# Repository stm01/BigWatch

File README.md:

# BigWatch
ATMega328 based DCF 77 synched Clock with 3D-printed Segments
/***
Readme will follow!

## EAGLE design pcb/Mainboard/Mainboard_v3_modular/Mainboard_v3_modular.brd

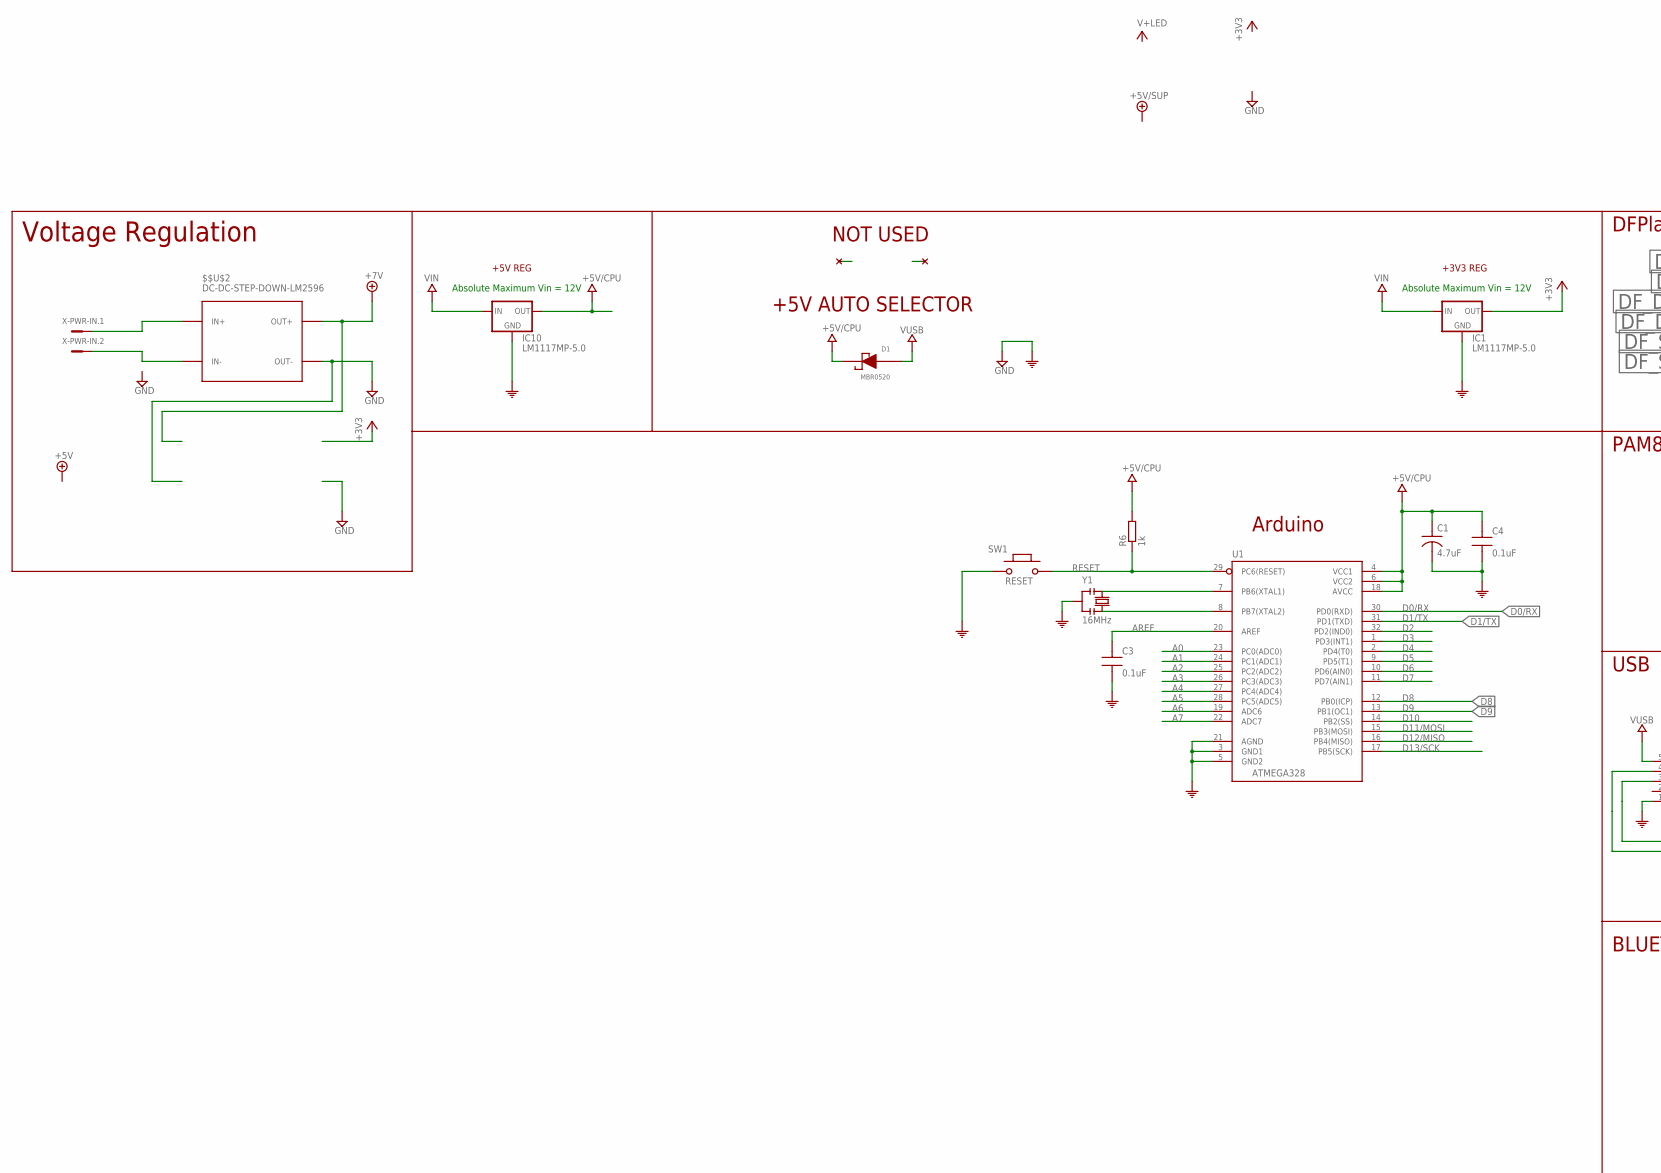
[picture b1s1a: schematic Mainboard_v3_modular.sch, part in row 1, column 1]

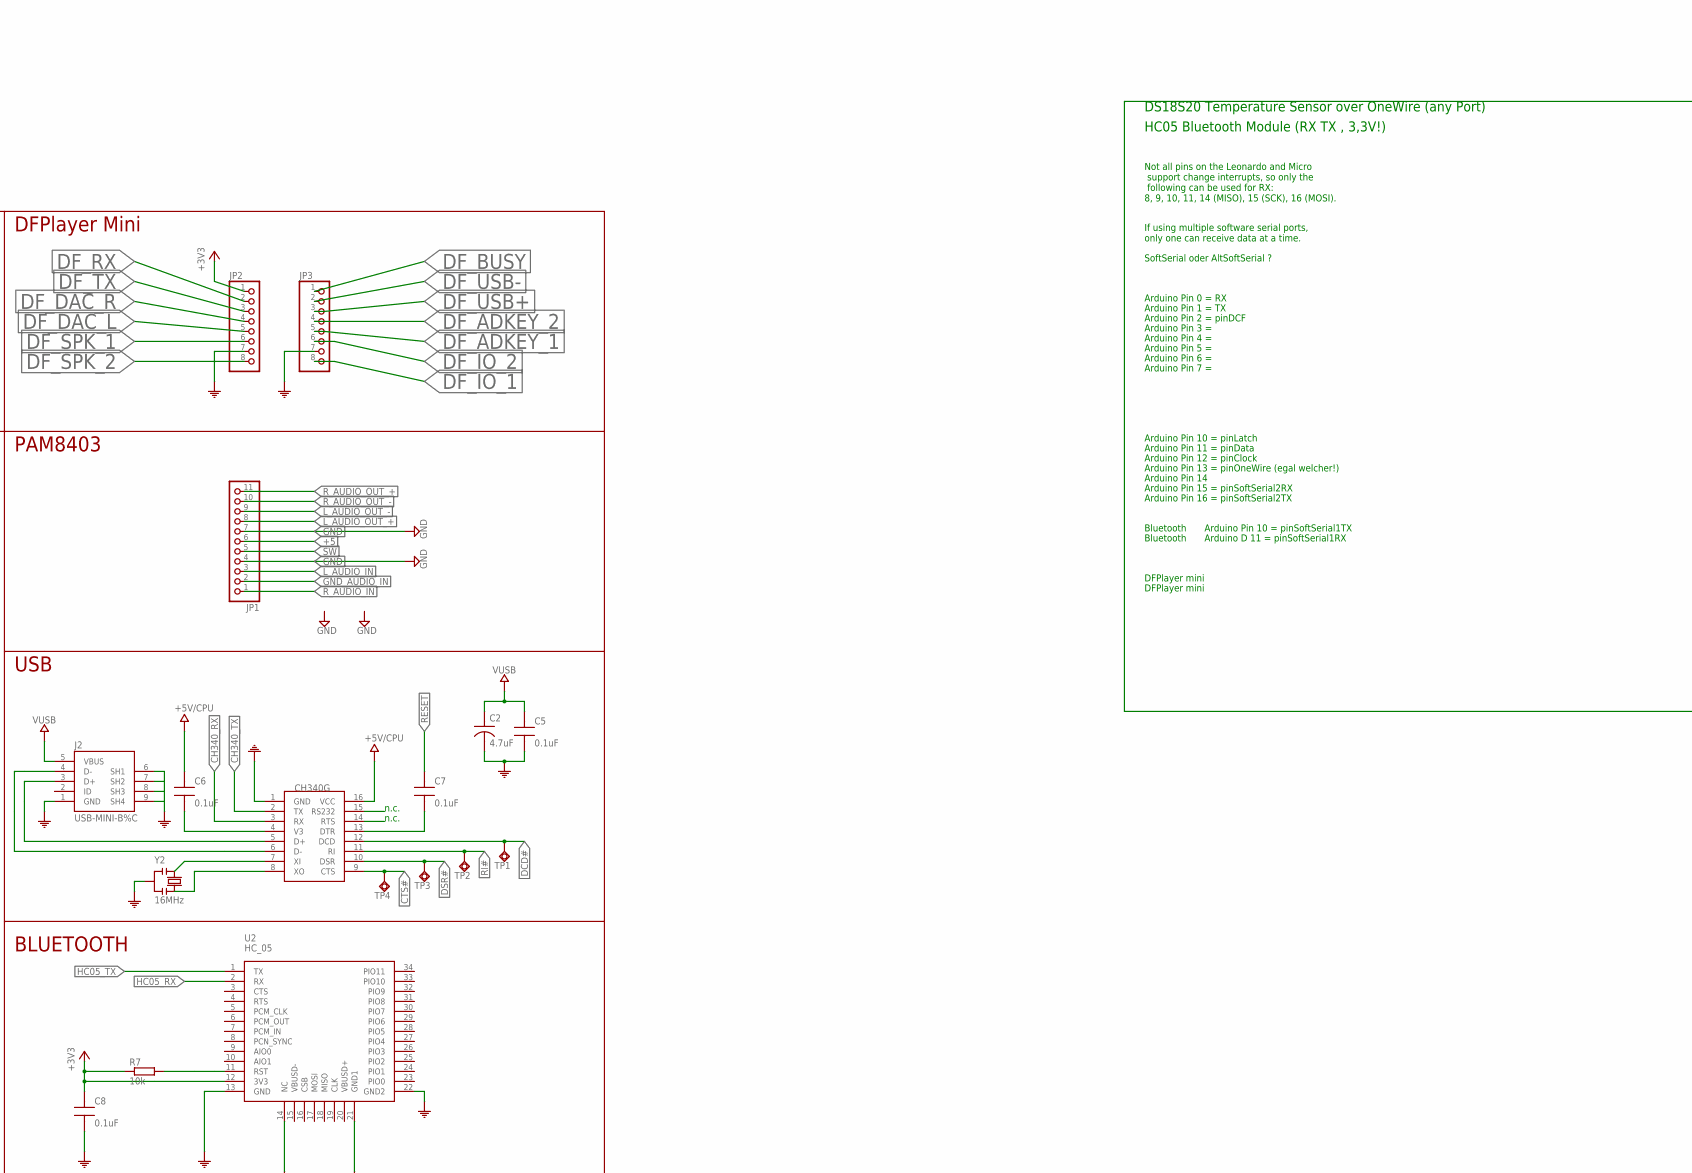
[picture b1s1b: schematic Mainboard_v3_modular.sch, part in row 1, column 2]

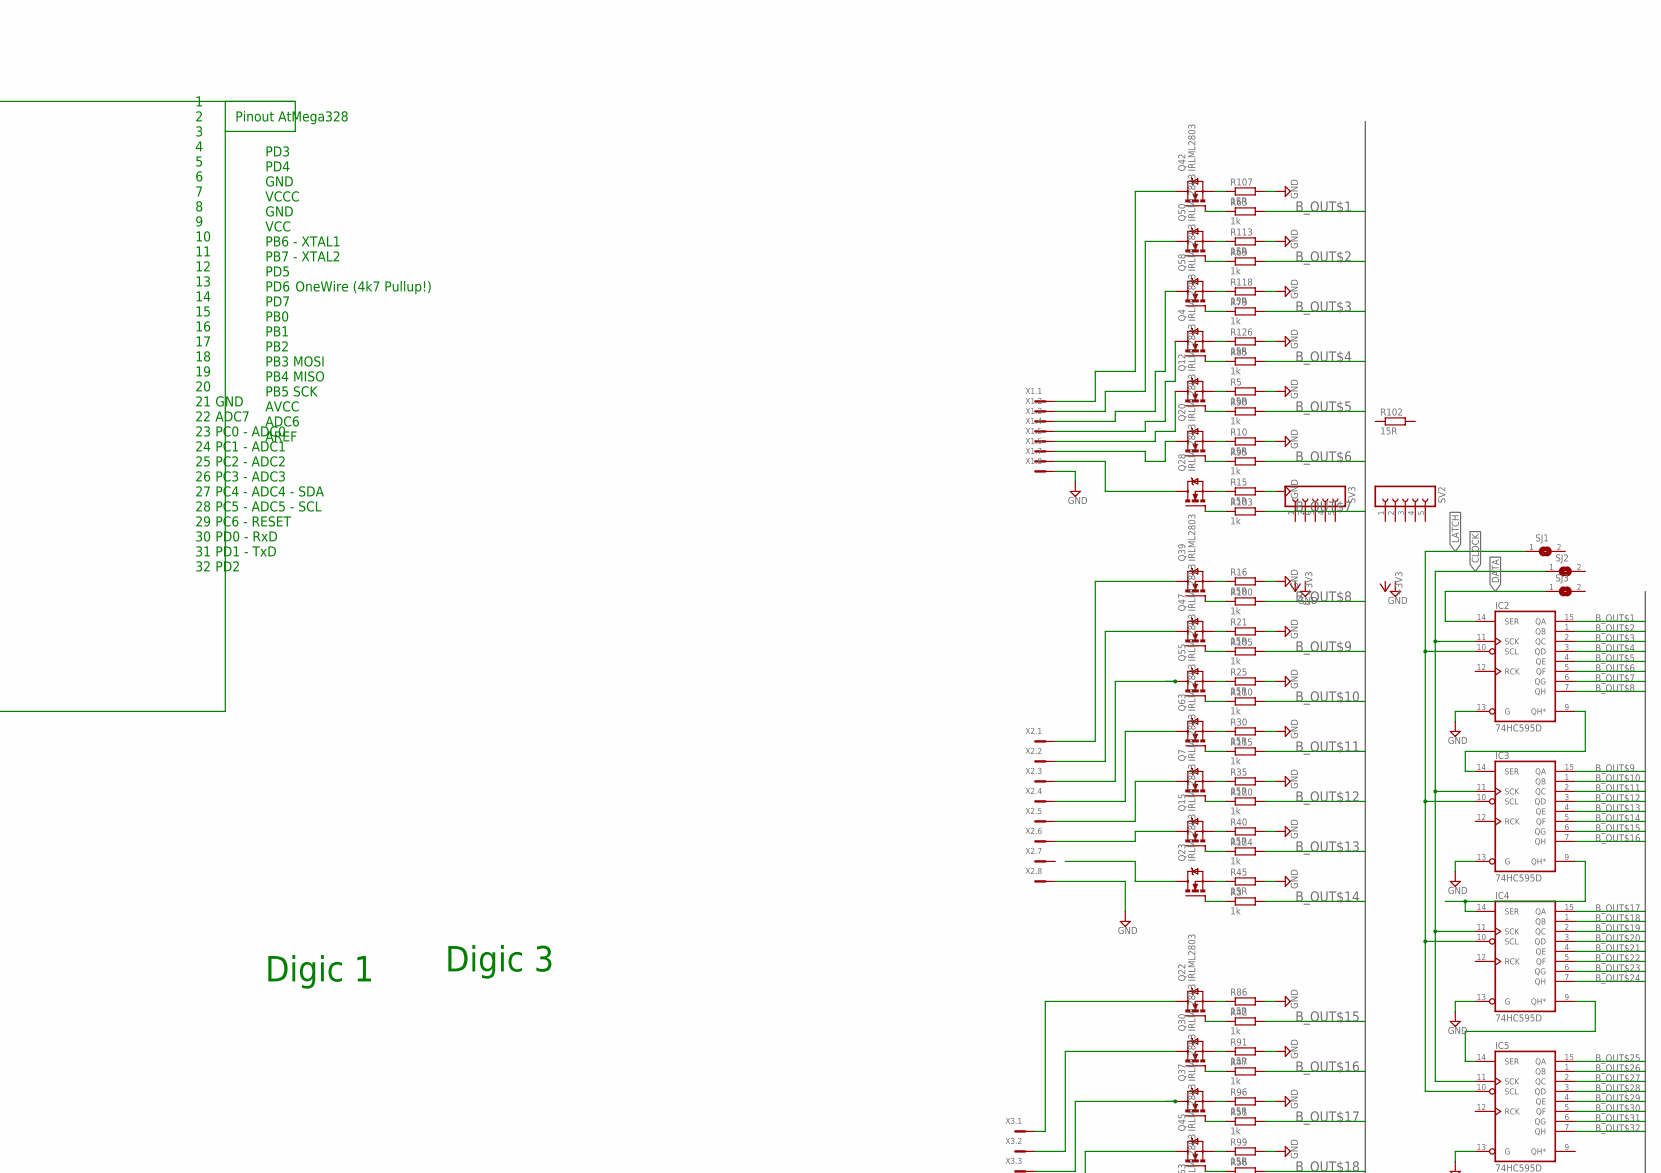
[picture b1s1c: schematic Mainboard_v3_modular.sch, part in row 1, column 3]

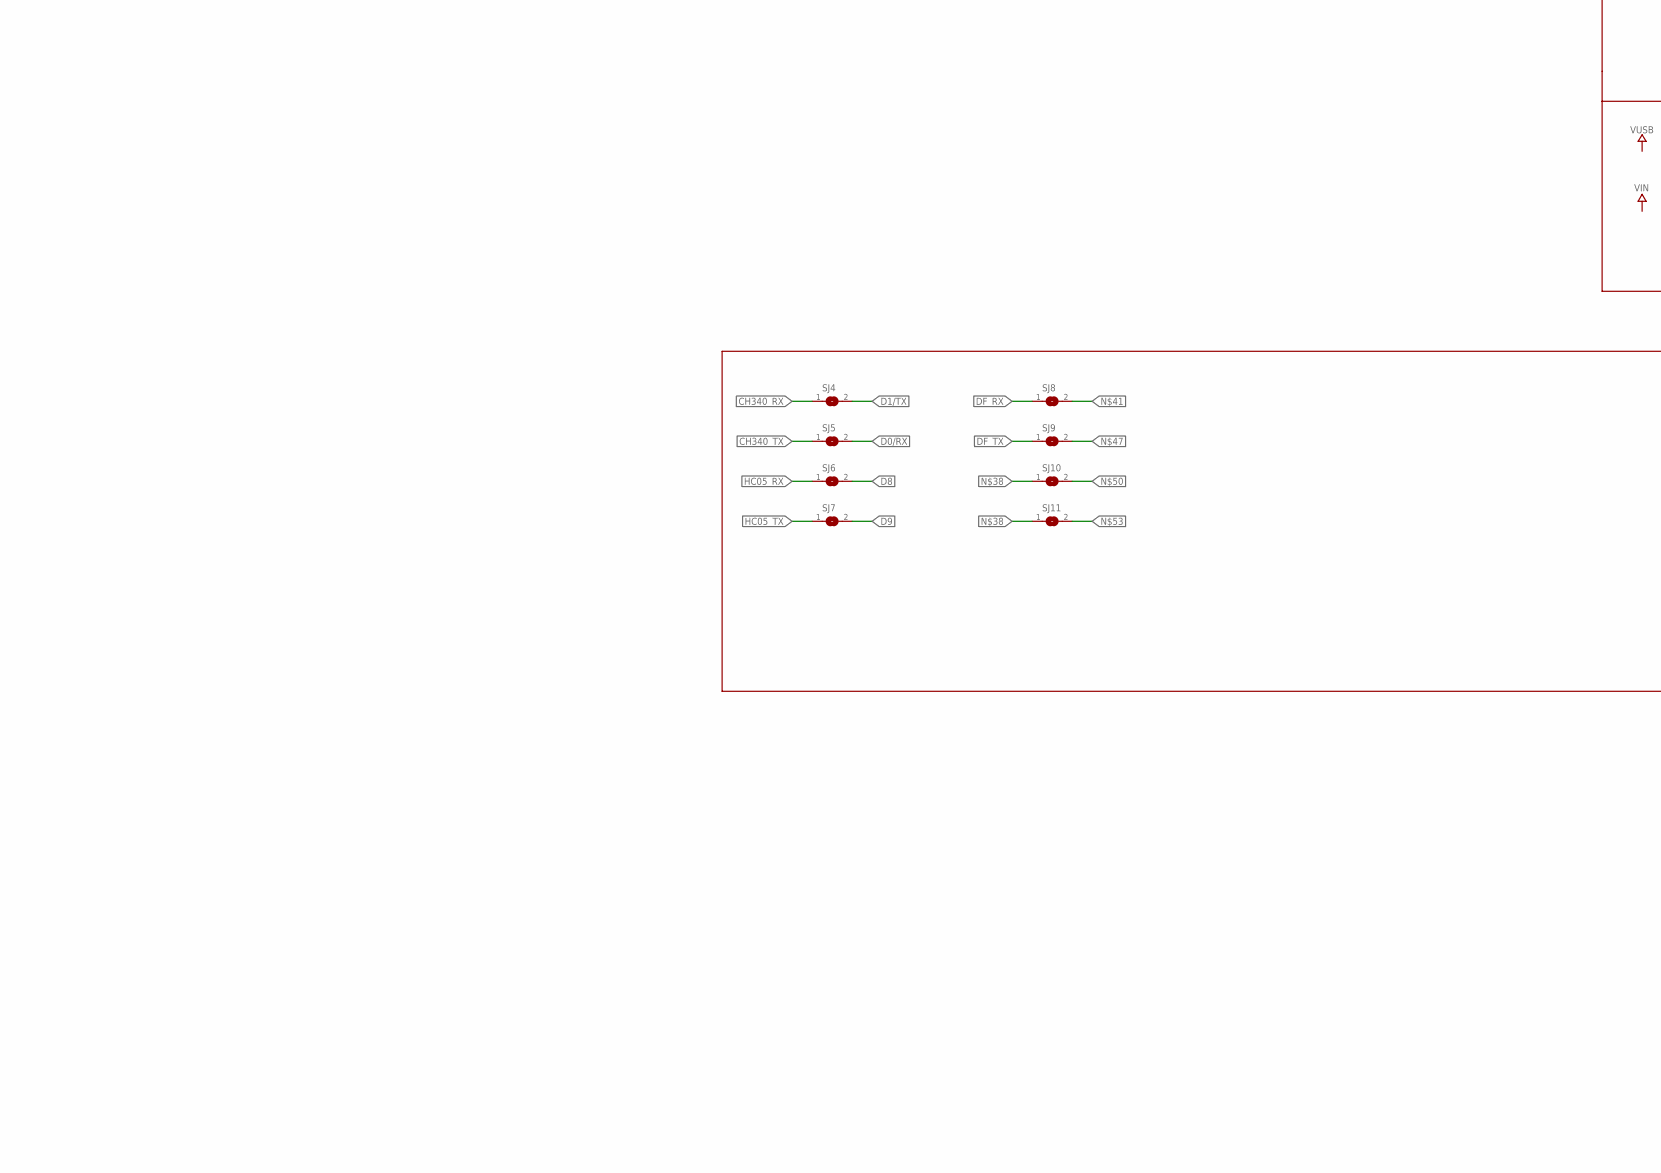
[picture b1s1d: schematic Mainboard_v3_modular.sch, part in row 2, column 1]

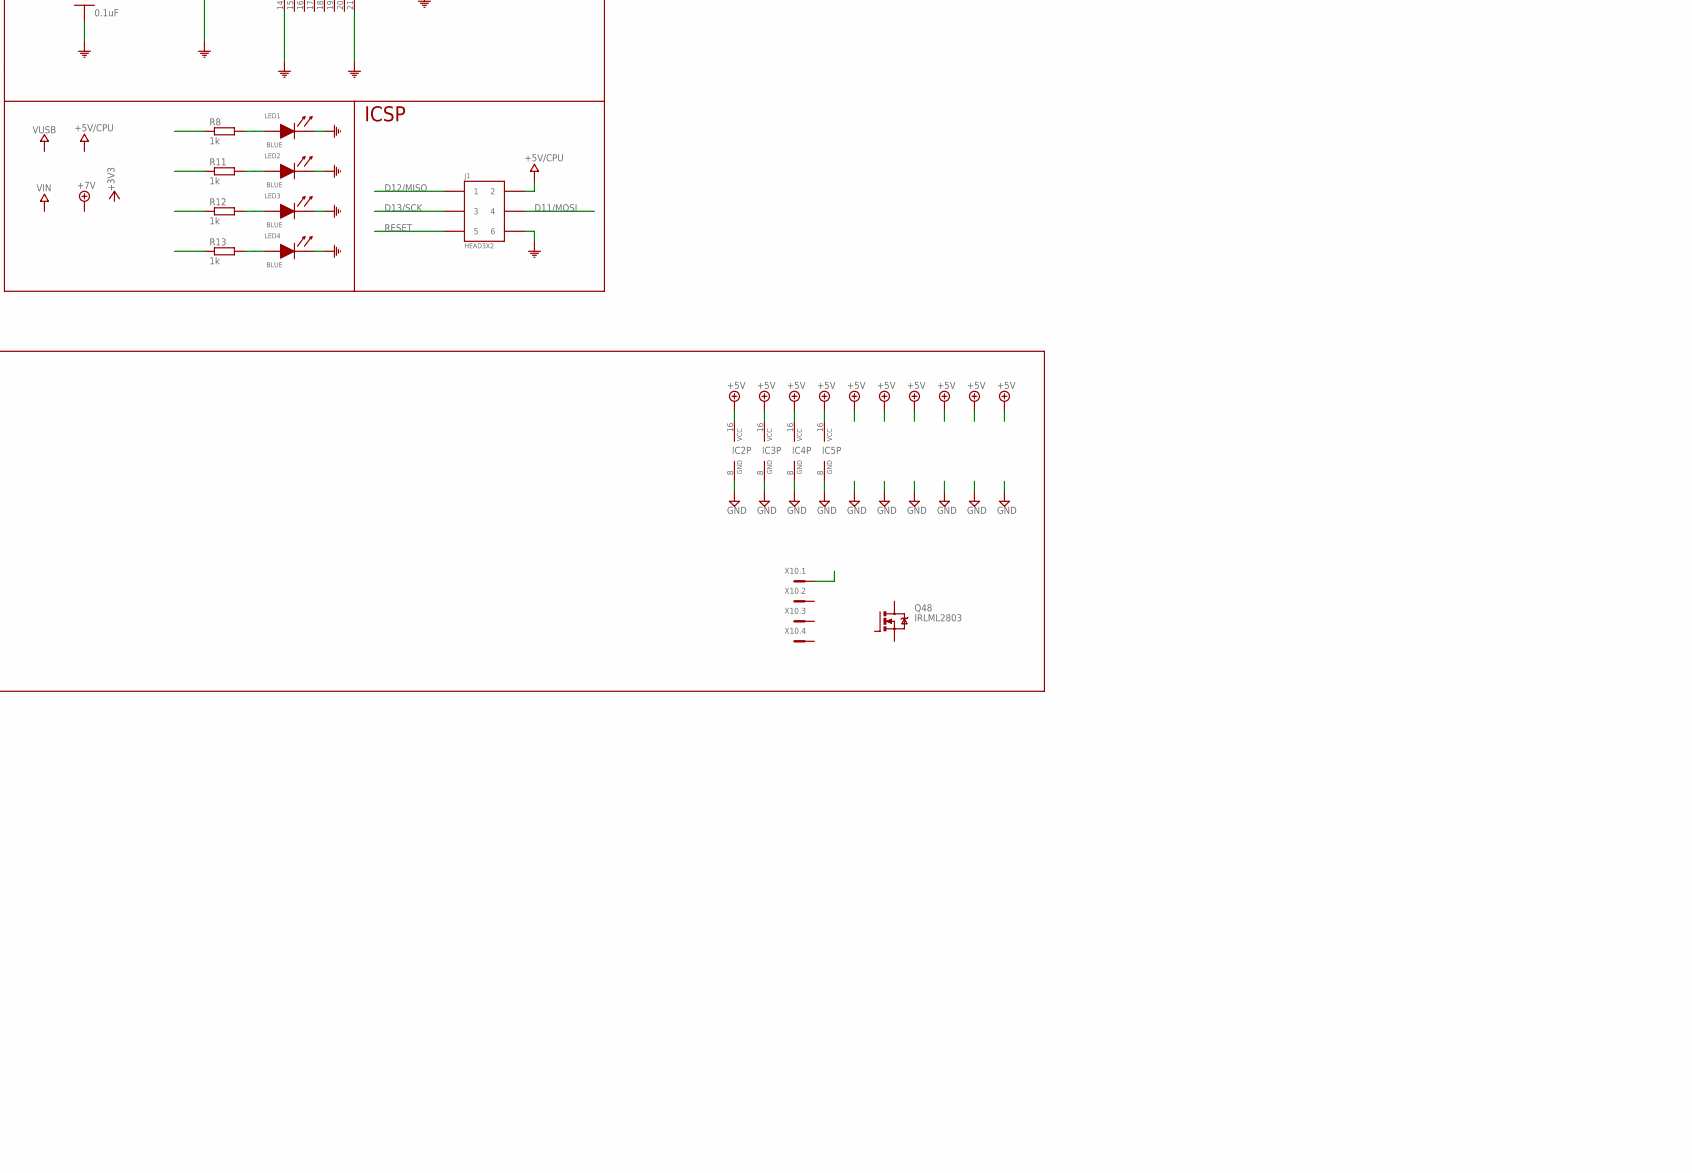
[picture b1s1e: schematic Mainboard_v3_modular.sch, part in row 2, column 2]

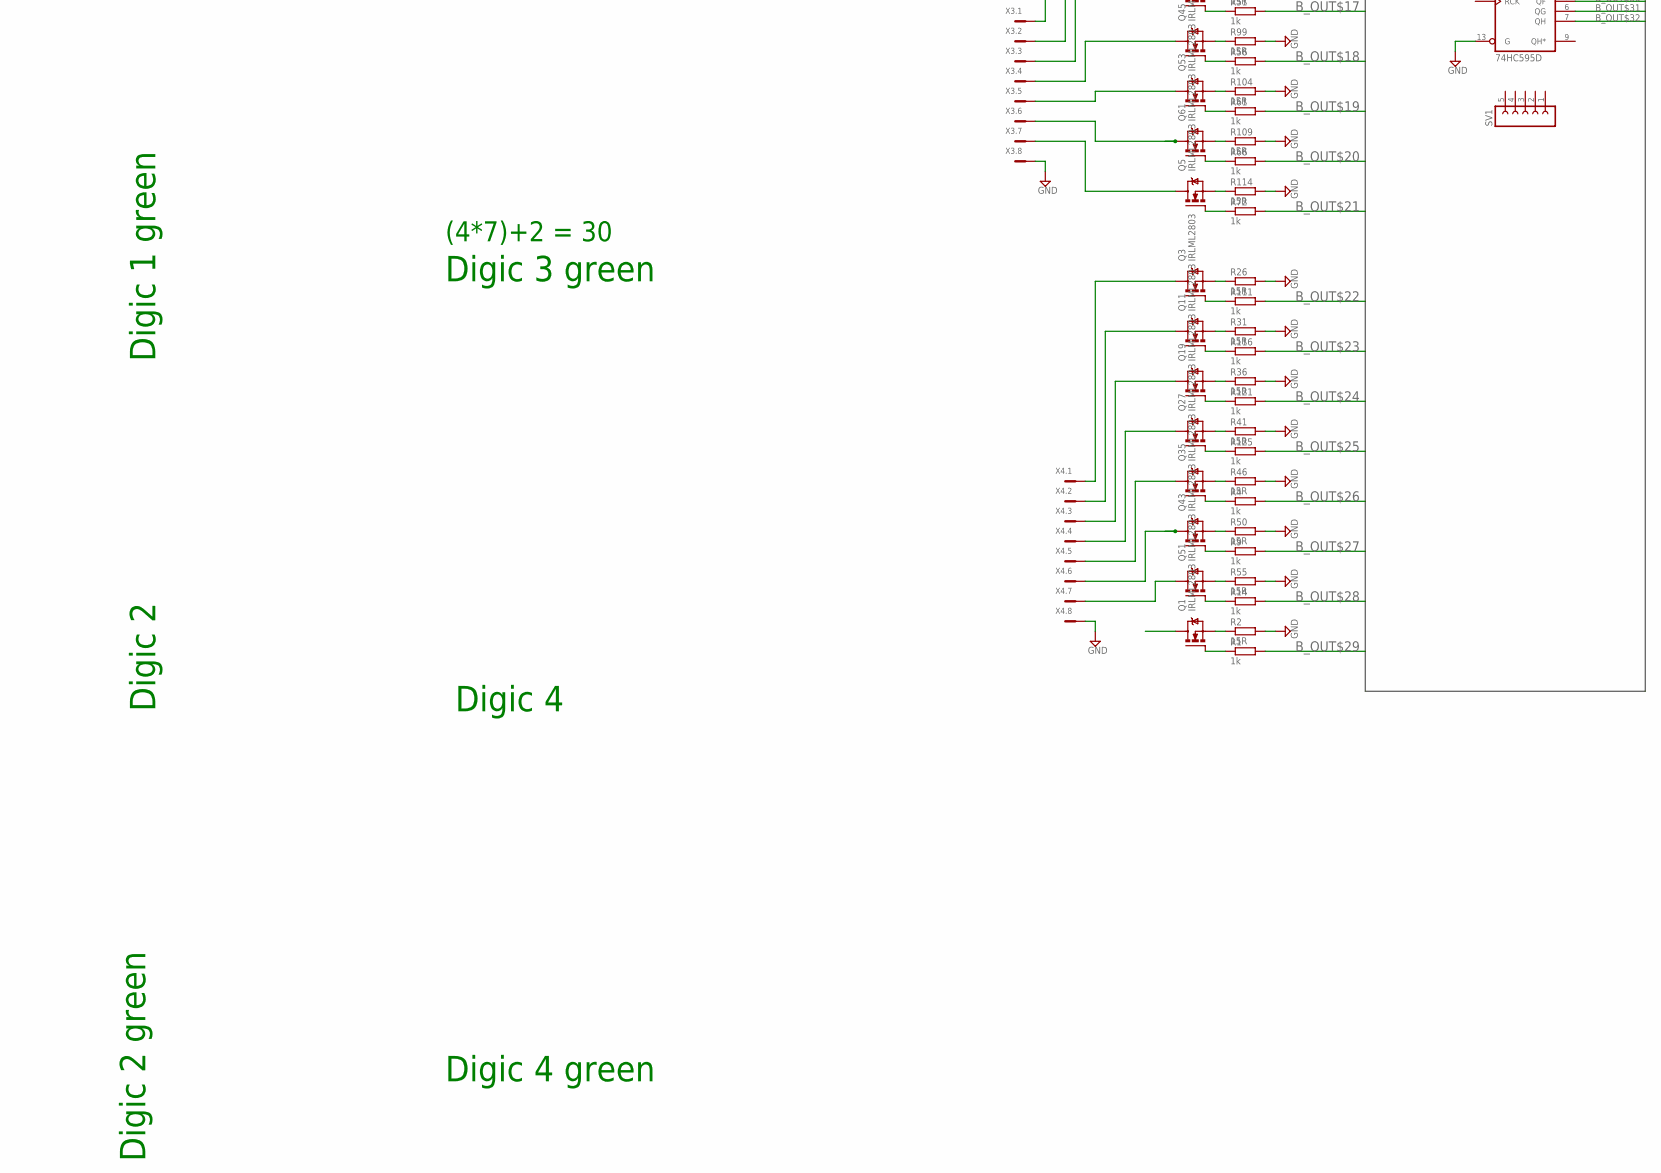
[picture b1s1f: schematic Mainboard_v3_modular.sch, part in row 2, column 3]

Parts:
$$U$2: DC-DC-STEP-DOWN-LM2596
C1, C2: 4.7uF; TAN-A
C3, C4, C5, C6, C7, C8: 0.1uF; CAP0805-NP
D1: MBR0520; SOD-123
IC1, IC10: LM1117MP-5.0; SOT223
IC2, IC3, IC4, IC5: 74HC595D; SO16
J1: HEAD3X2
J2: USB-MINI-B%C; USB-MINI-B_2
JP1: PINHD-1X11_2.00; 1X11M
JP2, JP3: PINHD-1X8; 1X08
LED1, LED2, LED3, LED4: BLUE; LED0805
Q1, Q3, Q4, Q5, Q7, Q11, Q12, Q15, Q19, Q20, Q22, Q23, Q27, Q28, Q30, Q35, Q37, Q39, Q42, Q43, Q45, Q47, Q48, Q50, Q51, Q53, Q55, Q58, Q61, Q63: IRLML2803; MICRO3
R1, R3, R4, R9, R14, R42, R47, R51, R56, R61, R63, R66, R69, R72, R79, R85, R90, R95, R100, R103, R105, R110, R111, R115, R116, R120, R121, R124, R125: 1k; M0805
R2, R5, R10, R15, R16, R21, R25, R26, R30, R31, R35, R36, R40, R41, R45, R46, R50, R55, R86, R91, R96, R99, R102, R104, R107, R109, R113, R114, R118, R126: 15R; M1206
R6, R8, R11, R12, R13: 1k; M1206
R7: 10k; M1206
SJ1, SJ2, SJ3, SJ4, SJ5, SJ6, SJ7, SJ8, SJ9, SJ10, SJ11: SJ
SV1, SV2, SV3: FE05-1
SW1: RESET; 157SW
TP1, TP2, TP3, TP4: TPSQTP14R; TP14R
U1: ATMEGA328; QFP032
U2: HC_05; BLUETOOTH_SMD
U$9: CH340G; SOIC16
X1, X2, X3, X4: MCV8-LOCK
X10: MCV4-LOCK
X-PWR-IN: MCV2-LOCK
Y1, Y2: 16MHz; RESONATOR

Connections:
+3V3: C8.1, IC1.2 (OUT), IC1.4 (OUT), JP2.1, R7.1, U2.12 (3V3)
+5: JP1.6
+5V: C1.1, C4.1, C6.1, D1.1 (CA), IC2.16 (VCC), IC3.16 (VCC), IC4.16 (VCC), IC5.16 (VCC), IC10.2 (OUT), IC10.4 (OUT), J1.2, R6.2, U1.4 (VCC1), U1.6 (VCC2), U1.18 (AVCC), U$9.16 (VCC)
+7V: $$U$2.OUT+
A0: U1.23 (PC0(ADC0))
A1: U1.24 (PC1(ADC1))
A2: U1.25 (PC2(ADC2))
A3: U1.26 (PC3(ADC3))
A4: U1.27 (PC4(ADC4))
A5: U1.28 (PC5(ADC5))
A6: U1.19 (ADC6)
A7: U1.22 (ADC7)
AREF: C3.1, U1.20 (AREF)
B_OUT$1: IC2.15 (QA), R63.2
B_OUT$2: IC2.1 (QB), R69.2
B_OUT$3: IC2.2 (QC), R79.2
B_OUT$4: IC2.3 (QD), R85.2
B_OUT$5: IC2.4 (QE), R90.2
B_OUT$6: IC2.5 (QF), R95.2
B_OUT$7: IC2.6 (QG), R103.2
B_OUT$8: IC2.7 (QH), R100.2
B_OUT$9: IC3.15 (QA), R105.2
B_OUT$10: IC3.1 (QB), R110.2
B_OUT$11: IC3.2 (QC), R115.2
B_OUT$12: IC3.3 (QD), R120.2
B_OUT$13: IC3.4 (QE), R124.2
B_OUT$14: IC3.5 (QF), R3.2
B_OUT$15: IC3.6 (QG), R42.2
B_OUT$16: IC3.7 (QH), R47.2
B_OUT$17: IC4.15 (QA), R51.2
B_OUT$18: IC4.1 (QB), R56.2
B_OUT$19: IC4.2 (QC), R61.2
B_OUT$20: IC4.3 (QD), R66.2
B_OUT$21: IC4.4 (QE), R72.2
B_OUT$22: IC4.5 (QF), R111.2
B_OUT$23: IC4.6 (QG), R116.2
B_OUT$24: IC4.7 (QH), R121.2
B_OUT$25: IC5.15 (QA), R125.2
B_OUT$26: IC5.1 (QB), R4.2
B_OUT$27: IC5.2 (QC), R9.2
B_OUT$28: IC5.3 (QD), R14.2
B_OUT$29: IC5.4 (QE), R1.2
B_OUT$30: IC5.5 (QF)
B_OUT$31: IC5.6 (QG)
B_OUT$32: IC5.7 (QH)
CH340_RX: SJ4.1, U$9.3 (RX)
CH340_TX: SJ5.1, U$9.2 (TX)
CLOCK: IC2.11 (SCK), IC3.11 (SCK), IC4.11 (SCK), IC5.11 (SCK), SJ2.1
COM: C1.2, C2.2, C3.2, C4.2, C5.2, C8.2, IC1.1 (GND), IC10.1 (GND), J1.6, J2.1 (GND), J2.6 (SH1), J2.7 (SH2), J2.8 (SH3), J2.9 (SH4), JP2.7, JP3.7, LED1.1 (CA), LED2.1 (CA), LED3.1 (CA), LED4.1 (CA), SW1.1, U1.3 (GND1), U1.5 (GND2), U1.21 (AGND), U2.13 (GND), U2.14 (NC), U2.21 (GND1), U2.22 (GND2), U$9.1 (GND), Y1.2, Y2.2
CTS#: TP4.TP, U$9.9 (CTS)
D0/RX: SJ5.2, U1.30 (PD0(RXD))
D1/TX: SJ4.2, U1.31 (PD1(TXD))
D2: U1.32 (PD2(IND0))
D3: U1.1 (PD3(INT1))
D4: U1.2 (PD4(T0))
D5: U1.9 (PD5(T1))
D6: U1.10 (PD6(AIN0))
D7: U1.11 (PD7(AIN1))
D8: SJ6.2, U1.12 (PB0(ICP))
D9: SJ7.2, U1.13 (PB1(OC1))
D10: U1.14 (PB2(SS))
D11/MOSI: J1.4, U1.15 (PB3(MOSI))
D12/MISO: J1.1, U1.16 (PB4(MISO))
D13/SCK: J1.3, U1.17 (PB5(SCK))
DATA: IC2.14 (SER), SJ3.1
DCD#: TP1.TP, U$9.12 (DCD)
DF_ADKEY_1: JP3.5
DF_ADKEY_2: JP3.4
DF_BUSY: JP3.1
DF_DAC_L: JP2.5
DF_DAC_R: JP2.4
DF_IO_1: JP3.8
DF_IO_2: JP3.6
DF_RX: JP2.2, SJ8.1
DF_SPK_1: JP2.6
DF_SPK_2: JP2.8
DF_TX: JP2.3, SJ9.1
DF_USB+: JP3.3
DF_USB-: JP3.2
DSR#: TP3.TP, U$9.10 (DSR)
GND: $$U$2.OUT-, IC2.8 (GND), IC2.13 (G), IC3.8 (GND), IC3.13 (G), IC4.8 (GND), IC4.13 (G), IC5.8 (GND), IC5.13 (G), JP1.4, JP1.7, R2.2, R5.2, R10.2, R15.2, R16.2, R21.2, R25.2, R26.2, R30.2, R31.2, R35.2, R36.2, R40.2, R41.2, R45.2, R46.2, R50.2, R55.2, R86.2, R91.2, R96.2, R99.2, R104.2, R107.2, R109.2, R113.2, R114.2, R118.2, R126.2, X1.8, X2.8, X3.8, X4.8
GND_AUDIO_IN: JP1.2
HC05_RX: SJ6.1, U2.2 (RX)
HC05_TX: SJ7.1, U2.1 (TX)
LATCH: IC2.10 (SCL), IC3.10 (SCL), IC4.10 (SCL), IC5.10 (SCL), SJ1.1
L_AUDIO_IN: JP1.3
L_AUDIO_OUT_+: JP1.8
L_AUDIO_OUT_-: JP1.9
unnamed: U1.8 (PB7(XTAL2)), Y1.3
unnamed: U1.7 (PB6(XTAL1)), Y1.1
unnamed: LED1.2 (AN), R8.2
unnamed: $$U$2.IN+, X-PWR-IN.1
unnamed: J2.3 (D+), U$9.5 (D+)
unnamed: J2.4 (D-), U$9.6 (D-)
unnamed: $$U$2.IN-, X-PWR-IN.2
unnamed: Q3.3 (D), X4.1
unnamed: Q1.2 (S), R2.1
unnamed: IC2.9 (QH*), IC3.14 (SER)
unnamed: Q1.1 (G), R1.1
unnamed: IC3.9 (QH*), IC4.14 (SER)
unnamed: Q39.3 (D), X2.1
unnamed: Q55.3 (D), X2.3
unnamed: Q19.3 (D), X4.3
unnamed: Q63.3 (D), X2.4
unnamed: Q7.3 (D), X2.5
unnamed: IC4.9 (QH*), IC5.14 (SER)
unnamed: Q11.3 (D), X4.2
unnamed: Q27.3 (D), X4.4
unnamed: Q35.3 (D), X4.5
unnamed: Q5.3 (D), X3.7
unnamed: Q51.3 (D), X4.7
unnamed: U$9.7 (XI), Y2.1
unnamed: U$9.8 (XO), Y2.3
unnamed: LED2.2 (AN), R11.2
unnamed: LED3.2 (AN), R12.2
unnamed: C6.2, U$9.4 (V3)
unnamed: C7.2, U$9.13 (DTR)
unnamed: SJ10.1, SJ11.1
unnamed: Q39.2 (S), R16.1
unnamed: Q39.1 (G), R100.1
unnamed: Q47.2 (S), R21.1
unnamed: Q47.1 (G), R105.1
unnamed: R7.2, U2.11 (RST)
unnamed: Q55.2 (S), R25.1
unnamed: Q55.1 (G), R110.1
unnamed: Q63.2 (S), R30.1
unnamed: Q63.1 (G), R115.1
unnamed: Q7.2 (S), R35.1
unnamed: Q7.1 (G), R120.1
unnamed: Q15.2 (S), R40.1
unnamed: Q15.1 (G), R124.1
unnamed: LED4.2 (AN), R13.2
unnamed: Q23.2 (S), R45.1
unnamed: Q23.1 (G), R3.1
unnamed: Q15.3 (D), X2.6
unnamed: Q47.3 (D), X2.2
unnamed: Q22.2 (S), R86.1
unnamed: Q22.1 (G), R42.1
unnamed: Q30.2 (S), R91.1
unnamed: Q30.1 (G), R47.1
unnamed: Q37.2 (S), R96.1
unnamed: Q37.1 (G), R51.1
unnamed: Q45.2 (S), R99.1
unnamed: Q45.1 (G), R56.1
unnamed: Q53.2 (S), R104.1
unnamed: Q53.1 (G), R61.1
unnamed: Q61.2 (S), R109.1
unnamed: Q61.1 (G), R66.1
unnamed: Q5.2 (S), R114.1
unnamed: Q5.1 (G), R72.1
unnamed: Q61.3 (D), X3.6
unnamed: Q53.3 (D), X3.5
unnamed: Q45.3 (D), X3.4
unnamed: Q37.3 (D), X3.3
unnamed: Q30.3 (D), X3.2
unnamed: Q22.3 (D), X3.1
unnamed: Q3.2 (S), R26.1
unnamed: Q3.1 (G), R111.1
unnamed: Q11.2 (S), R31.1
unnamed: Q11.1 (G), R116.1
unnamed: Q19.2 (S), R36.1
unnamed: Q19.1 (G), R121.1
unnamed: Q27.2 (S), R41.1
unnamed: Q27.1 (G), R125.1
unnamed: Q35.2 (S), R46.1
unnamed: Q35.1 (G), R4.1
unnamed: Q43.2 (S), R50.1
unnamed: Q43.1 (G), R9.1
unnamed: Q51.2 (S), R55.1
unnamed: Q51.1 (G), R14.1
unnamed: Q43.3 (D), X4.6
unnamed: Q58.2 (S), R118.1
unnamed: Q42.2 (S), R107.1
unnamed: Q42.1 (G), R63.1
unnamed: Q58.1 (G), R79.1
unnamed: Q50.2 (S), R113.1
unnamed: Q50.1 (G), R69.1
unnamed: Q4.2 (S), R126.1
unnamed: Q4.1 (G), R85.1
unnamed: Q12.2 (S), R5.1
unnamed: Q12.1 (G), R90.1
unnamed: Q20.2 (S), R10.1
unnamed: Q20.1 (G), R95.1
unnamed: Q28.2 (S), R15.1
unnamed: Q28.1 (G), R103.1
unnamed: Q28.3 (D), X1.7
unnamed: Q20.3 (D), X1.6
unnamed: Q12.3 (D), X1.5
unnamed: Q4.3 (D), X1.4
unnamed: Q58.3 (D), X1.3
unnamed: Q50.3 (D), X1.2
unnamed: Q42.3 (D), X1.1
RESET: C7.1, J1.5, R6.1, SW1.2, U1.29 (PC6(RESET))
RI#: TP2.TP, U$9.11 (RI)
R_AUDIO_IN: JP1.1
R_AUDIO_OUT_+: JP1.11
R_AUDIO_OUT_-: JP1.10
SW: JP1.5
VIN: IC1.3 (IN), IC10.3 (IN)
VUSB: C2.1, C5.1, D1.2 (AN), J2.5 (VBUS)

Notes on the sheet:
Arduino
+5V REG
ICSP
+5V AUTO SELECTOR
NOT USED
Absolute Maximum Vin = 12V
Voltage Regulation
(4*7)+2 = 30
Digic 1
Digic 1 green
Digic 2 green
Digic 3 green
Digic 4 green
Digic 4
Digic 3
Digic 2
Pinout AtMega328
1 2 3 4 5 6 7 8 9 10 11 12 13 14 15 16 17 18 19 20 21 22 23 24 25 26 27 28 29 30 31 32
PD3 PD4 GND VCCC GND VCC
PB6 - XTAL1 PB7 - XTAL2 PD5 PD6 PD7 PB0 PB1 PB2 PB3 MOSI PB4 MISO PB5 SCK AVCC ADC6 AREF
GND ADC7 PC0 - ADC0 PC1 - ADC1 PC2 - ADC2 PC3 - ADC3 PC4 - ADC4 - SDA PC5 - ADC5 - SCL PC6 - RESET PD0 - RxD PD1 - TxD PD2
OneWire (4k7 Pullup!)
DS18S20 Temperature Sensor over OneWire (any Port)
HC05 Bluetooth Module (RX TX , 3,3V!)
Not all pins on the Leonardo and Micro support change interrupts, so only the following can be used for RX: 8, 9, 10, 11, 14 (MISO), 15 (SCK), 16 (MOSI).
If using multiple software serial ports, only one can receive data at a time.
SoftSerial oder AltSoftSerial ?
Arduino Pin 10 = pinLatch
Arduino Pin 12 = pinClock
Arduino Pin 11 = pinData
Arduino Pin 13 = pinOneWire (egal welcher!)
Arduino Pin 15 = pinSoftSerial2RX
Arduino Pin 16 = pinSoftSerial2TX
Arduino Pin 10 = pinSoftSerial1TX
Arduino D 11 = pinSoftSerial1RX
Arduino Pin 14
Arduino Pin 0 = RX
Arduino Pin 1 = TX
Arduino Pin 2 = pinDCF
Arduino Pin 3 =

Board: 2 copper layers, 150 parts (0 on the bottom side), 161 nets, no tracks yet.

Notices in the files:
parts and their libraries:
diy_modules: Released under the Creative Commons Attribution 4.0 International License: http://creativecommons.org/licenses/by/4.0
